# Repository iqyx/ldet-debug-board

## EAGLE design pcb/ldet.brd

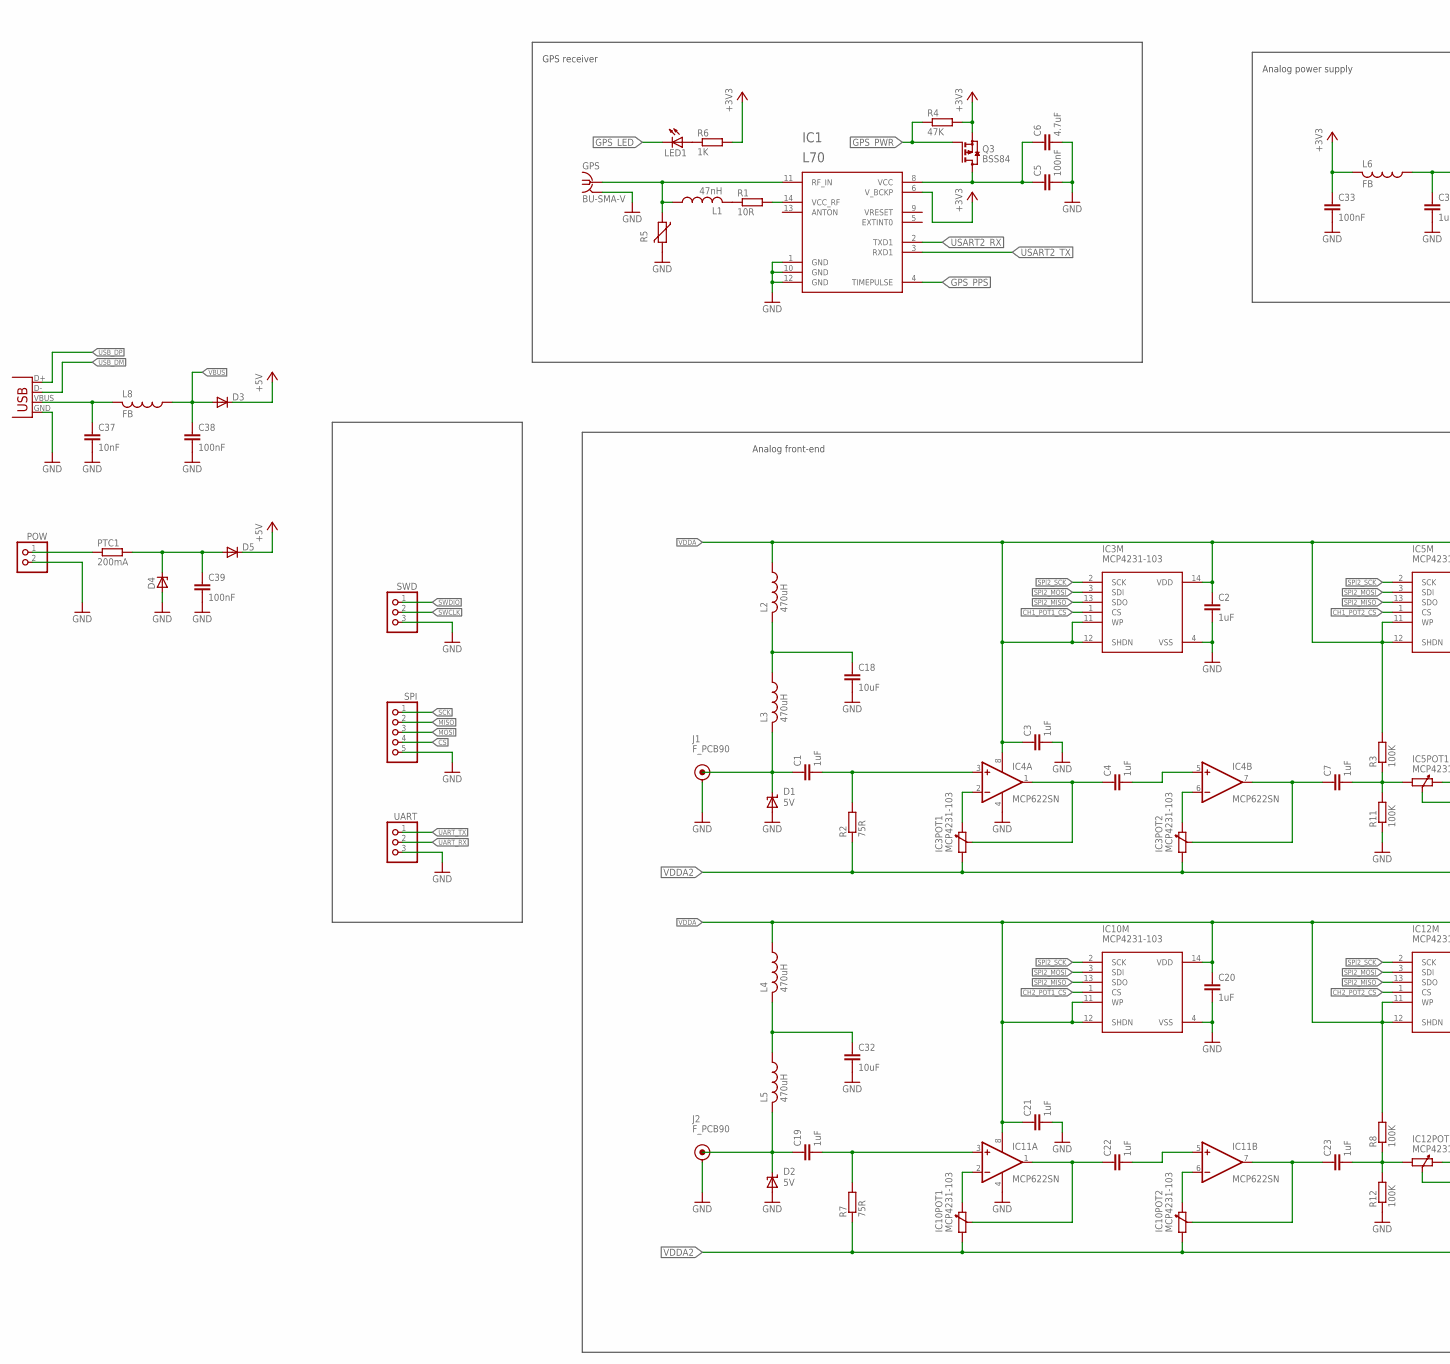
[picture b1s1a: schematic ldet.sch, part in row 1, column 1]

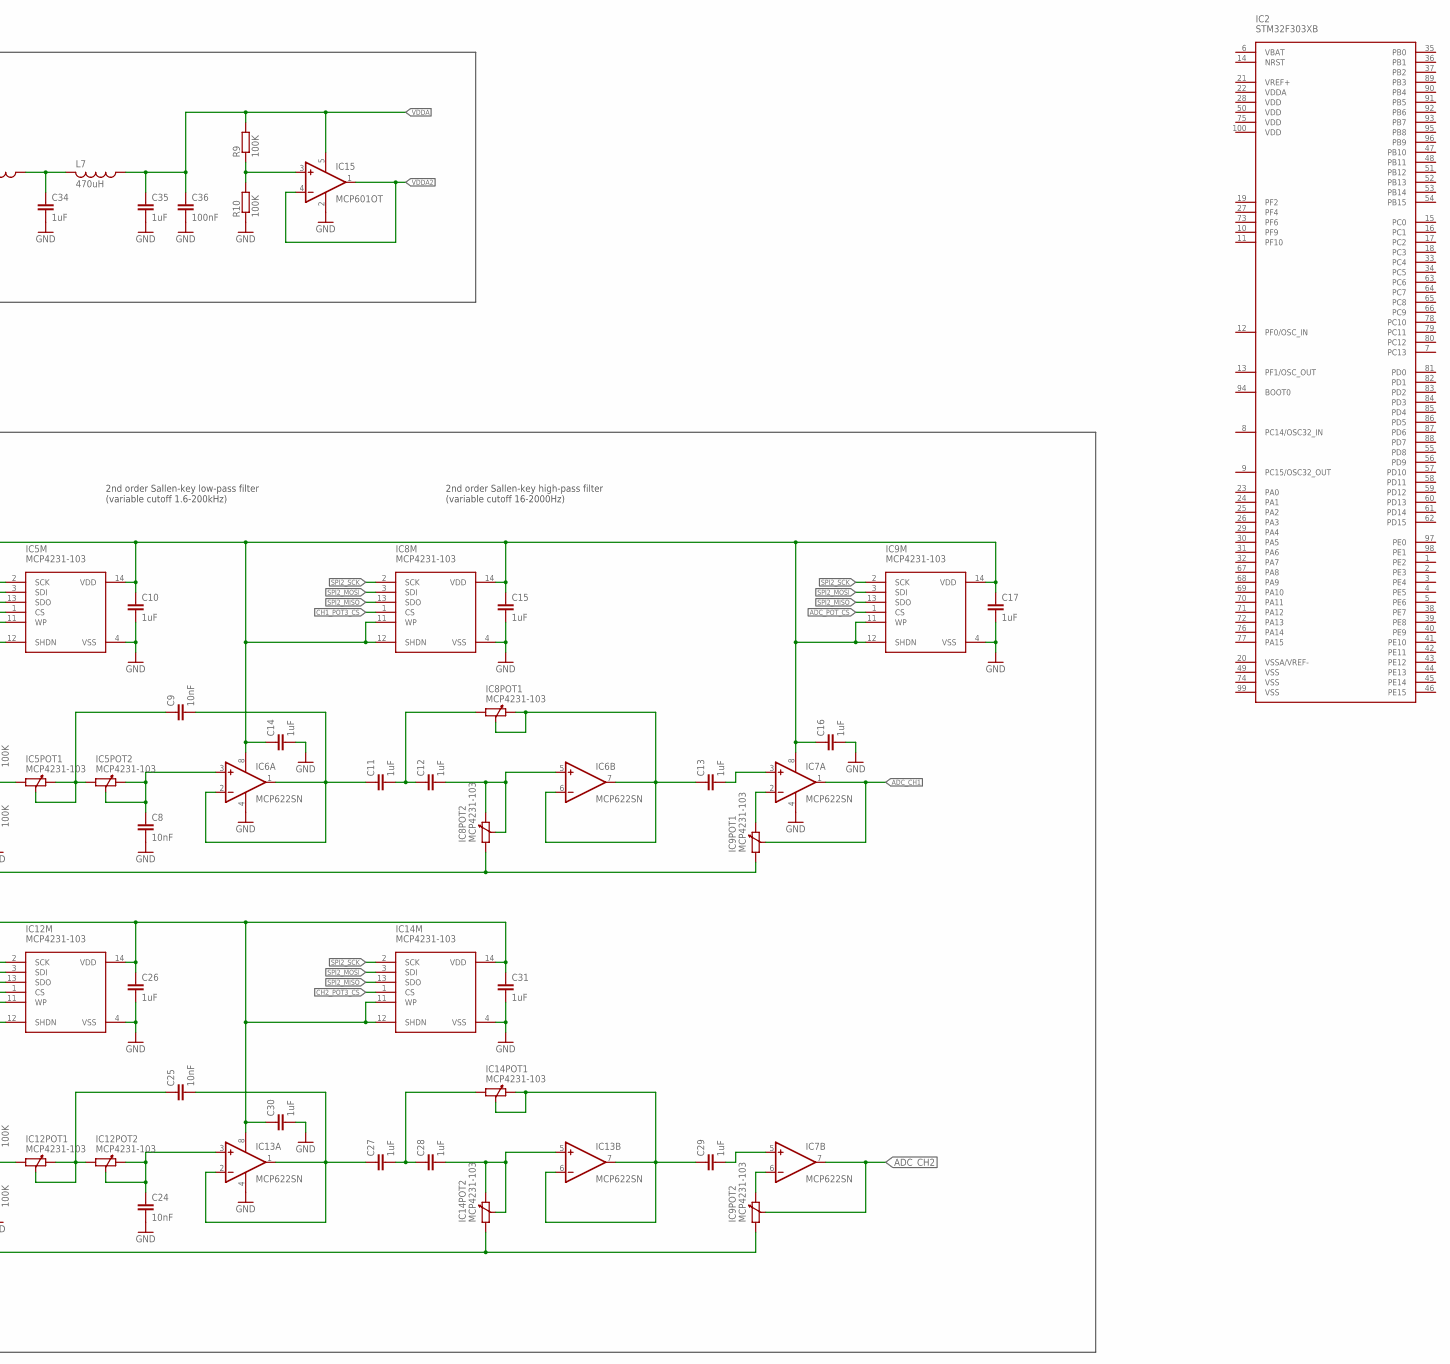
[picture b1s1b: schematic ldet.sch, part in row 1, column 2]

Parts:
C1, C2, C3, C4, C7, C10, C11, C12, C13, C14, C15, C16, C17, C19, C20, C21, C22, C23, C26, C27, C28, C29, C30, C31, C34, C35: 1uF; C0603
C5, C33, C36, C38, C39: 100nF; C0603
C6: 4.7uF; C0805
C8, C9, C24, C25, C37: 10nF; C0603
C18, C32: 10uF; C1206
D1, D2: 5V; SMBJ
D3, D5: DIODE-SOD123; SOD123
D4: ZENER-DIODESMB; SMB
GPS: BU-SMA-V
IC1: L70
IC2: STM32F303XB; TQFP100
IC3, IC5, IC8, IC9, IC10, IC12, IC14: MCP4231-103; SO14
IC4, IC6, IC7, IC11, IC13: MCP622SN; SO08
IC15: MCP601OT; SOT23-5
J1, J2: F_PCB90; F_PCB_90
L1: 47nH; L2012C
L2, L3, L4, L5, L7: 470uH; L3225M; MPN LQH32CN471K23L
L6, L8: FB; L2012C; MPN LQH32CN471K23L
LED1: LEDCHIP-LED0603; CHIP-LED0603
POW: PINHD-1X2; 1X02
PTC1: 200mA; R3225
Q3: BSS84; SOT23
R1: 10R; R0603
R2, R7: 75R; R0603
R3, R8, R9, R10, R11, R12: 100K; R0603
R4: 47K; R0603
R5: VARISTORCN0805; CT/CN0805
R6: 1K; R0603
SPI: PINHD-1X5; 1X05
SWD: PINHD-1X3; 1X03
UART: PINHD-1X3; 1X03
X1: USBPTH; USB-B-PTH

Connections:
+3V3: C33.1, IC1.6 (V_BCKP), L6.2, Q3.2 (S), R4.2, R6.2
+5V: D3.C, D5.C
ADC_CH1: IC7.1 (OUT), IC9.6 (W)
ADC_CH2: IC7.7 (OUT), IC9.9 (W)
ADC_POT_CS: IC9.1 (CS)
CH1_IN: C1.1, D1.C, J1.C (CENTER), L3.2
CH1_POT1_CS: IC3.1 (CS)
CH1_POT2_CS: IC5.1 (CS)
CH1_POT3_CS: IC8.1 (CS)
CH2_IN: C19.1, D2.C, J2.C (CENTER), L5.2
CH2_POT1_CS: IC10.1 (CS)
CH2_POT2_CS: IC12.1 (CS)
CH2_POT3_CS: IC14.1 (CS)
CS: SPI.4
GND: C2.2, C3.2, C5.2, C6.2, C8.2, C10.2, C14.2, C15.2, C16.2, C17.2, C18.2, C20.2, C21.2, C24.2, C26.2, C30.2, C31.2, C32.2, C33.2, C34.2, C35.2, C36.2, C37.2, C38.2, C39.2, D1.A, D2.A, D4.A, GPS.2, GPS.3 (2), GPS.4 (2), GPS.5 (2), IC1.1 (GND), IC1.10 (GND), IC1.12 (GND), IC3.4 (VSS), IC4.4 (V-), IC5.4 (VSS), IC6.4 (V-), IC7.4 (V-), IC8.4 (VSS), IC9.4 (VSS), IC10.4 (VSS), IC11.4 (V-), IC12.4 (VSS), IC13.4 (V-), IC14.4 (VSS), IC15.2 (V-), J1.S1 (SHIELD), J1.S2 (SHIELD), J1.S3 (SHIELD), J1.S4 (SHIELD), J2.S1 (SHIELD), J2.S2 (SHIELD), J2.S3 (SHIELD), J2.S4 (SHIELD), POW.2, R5.2, R10.1, R11.1, R12.1, SPI.5, SWD.3, UART.3, X1.GND
GPS_LED: LED1.C
GPS_PPS: IC1.4 (TIMEPULSE)
GPS_PWR: Q3.1 (G), R4.1
MISO: SPI.2
MOSI: SPI.3
unnamed: C1.2, IC4.3 (+IN), R2.2
unnamed: IC3.5 (B), IC4.2 (-IN)
unnamed: L1.2, R1.1
unnamed: GPS.1, IC1.11 (RF_IN), L1.1, R5.1
unnamed: IC1.14 (VCC_RF), R1.2
unnamed: C4.1, IC3.6 (W), IC4.1 (OUT)
unnamed: LED1.A, R6.1
unnamed: C5.1, C6.1, IC1.8 (VCC), Q3.3 (D)
unnamed: C4.2, IC4.5 (+IN)
unnamed: C7.1, IC3.9 (W), IC4.7 (OUT)
unnamed: IC3.10 (B), IC4.6 (-IN)
unnamed: C7.2, IC5.7 (A), R3.1, R11.2
unnamed: C9.1, IC5.5 (B), IC5.6 (W), IC5.8 (A)
unnamed: C8.1, IC5.9 (W), IC5.10 (B), IC6.3 (+IN)
unnamed: C9.2, C11.1, IC6.1 (OUT), IC6.2 (-IN)
unnamed: C11.2, C12.1, IC8.7 (A)
unnamed: C12.2, IC6.5 (+IN), IC8.9 (W), IC8.10 (B)
unnamed: C13.1, IC6.6 (-IN), IC6.7 (OUT), IC8.5 (B), IC8.6 (W)
unnamed: IC7.2 (-IN), IC9.5 (B)
unnamed: C13.2, IC7.3 (+IN)
unnamed: C18.1, L2.2, L3.1
unnamed: C19.2, IC11.3 (+IN), R7.2
unnamed: IC10.5 (B), IC11.2 (-IN)
unnamed: C22.1, IC10.6 (W), IC11.1 (OUT)
unnamed: C22.2, IC11.5 (+IN)
unnamed: C23.1, IC10.9 (W), IC11.7 (OUT)
unnamed: IC10.10 (B), IC11.6 (-IN)
unnamed: C23.2, IC12.7 (A), R8.1, R12.2
unnamed: C25.1, IC12.5 (B), IC12.6 (W), IC12.8 (A)
unnamed: C24.1, IC12.9 (W), IC12.10 (B), IC13.3 (+IN)
unnamed: C25.2, C27.1, IC13.1 (OUT), IC13.2 (-IN)
unnamed: C27.2, C28.1, IC14.7 (A)
unnamed: C28.2, IC13.5 (+IN), IC14.9 (W), IC14.10 (B)
unnamed: C29.1, IC13.6 (-IN), IC13.7 (OUT), IC14.5 (B), IC14.6 (W)
unnamed: C29.2, IC7.5 (+IN)
unnamed: C32.1, L4.2, L5.1
unnamed: IC7.6 (-IN), IC9.10 (B)
unnamed: C34.1, L6.1, L7.2
unnamed: C37.1, L8.2, X1.VBUS
unnamed: IC15.3 (+IN), R9.1, R10.2
unnamed: POW.1, PTC1.1
unnamed: C39.1, D4.C, D5.A, PTC1.2
SCK: SPI.1
SPI2_MISO: IC3.13 (SDO), IC5.13 (SDO), IC8.13 (SDO), IC9.13 (SDO), IC10.13 (SDO), IC12.13 (SDO), IC14.13 (SDO)
SPI2_MOSI: IC3.3 (SDI), IC5.3 (SDI), IC8.3 (SDI), IC9.3 (SDI), IC10.3 (SDI), IC12.3 (SDI), IC14.3 (SDI)
SPI2_SCK: IC3.2 (SCK), IC5.2 (SCK), IC8.2 (SCK), IC9.2 (SCK), IC10.2 (SCK), IC12.2 (SCK), IC14.2 (SCK)
SWCLK: SWD.2
SWDIO: SWD.1
UART_RX: UART.2
UART_TX: UART.1
USART2_RX: IC1.2 (TXD1)
USART2_TX: IC1.3 (RXD1)
USB_DM: X1.D-
USB_DP: X1.D+
VBUS: C38.1, D3.A, L8.1
VDDA: C2.1, C3.1, C10.1, C14.1, C15.1, C16.1, C17.1, C20.1, C21.1, C26.1, C30.1, C31.1, C35.1, C36.1, IC3.11 (WP), IC3.12 (SHDN), IC3.14 (VDD), IC4.8 (V+), IC5.11 (WP), IC5.12 (SHDN), IC5.14 (VDD), IC6.8 (V+), IC7.8 (V+), IC8.11 (WP), IC8.12 (SHDN), IC8.14 (VDD), IC9.11 (WP), IC9.12 (SHDN), IC9.14 (VDD), IC10.11 (WP), IC10.12 (SHDN), IC10.14 (VDD), IC11.8 (V+), IC12.11 (WP), IC12.12 (SHDN), IC12.14 (VDD), IC13.8 (V+), IC14.11 (WP), IC14.12 (SHDN), IC14.14 (VDD), IC15.5 (V+), L2.1, L4.1, L7.1, R3.2, R8.2, R9.2
VDDA2: IC3.7 (A), IC3.8 (A), IC8.8 (A), IC9.7 (A), IC9.8 (A), IC10.7 (A), IC10.8 (A), IC14.8 (A), IC15.1 (OUT), IC15.4 (-IN), R2.1, R7.1

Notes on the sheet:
GPS receiver
2nd order Sallen-key low-pass filter (variable cutoff 1.6-200kHz)
2nd order Sallen-key high-pass filter (variable cutoff 16-2000Hz)
Analog front-end
Analog power supply

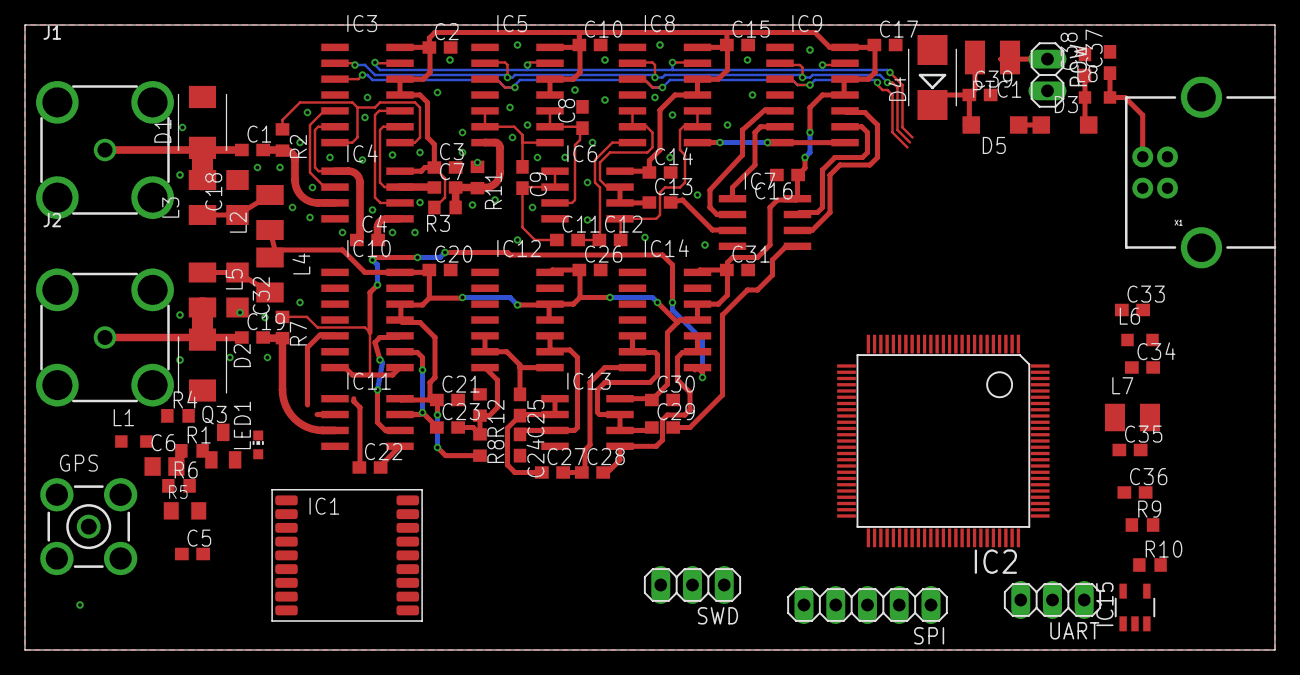
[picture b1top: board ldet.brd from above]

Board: 2 copper layers, 100.0 x 50.0 mm, 90 parts (0 on the bottom side), 56 nets.

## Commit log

2016-08-16 Add .gitignore file
2016-08-16 Draw schematic of the analog frontend

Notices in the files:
parts and their libraries:
SparkFun: Licensing: CC v3.0 Share-Alike You are welcome to use this library for commercial purposes.
